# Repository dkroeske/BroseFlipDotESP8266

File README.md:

# BroseFlipDotESP8266

Few months ago I bought some very old and dirty Brose Vollmatrix displays also known as flip dot of disk displays. With the use of the internet I reverse engineered the internals and hooked up an ESP8266 board. Using an MQTT broker I'm able to display text and bitmaps (black and white e.g. 112x16 pixels). After some time the display will enter idle mode where is makes a nice clock. The display also contains a backlight that can be controlled using MQTT.

MQTT enabled Brose FlipDot

{
	"message": {
		"content": "DIEDERICH",
		"x": 0,
		"y": 0,
		"font": 2,
		"display_time": 20
	},
	"backlight": {
		"on": true
	}
}

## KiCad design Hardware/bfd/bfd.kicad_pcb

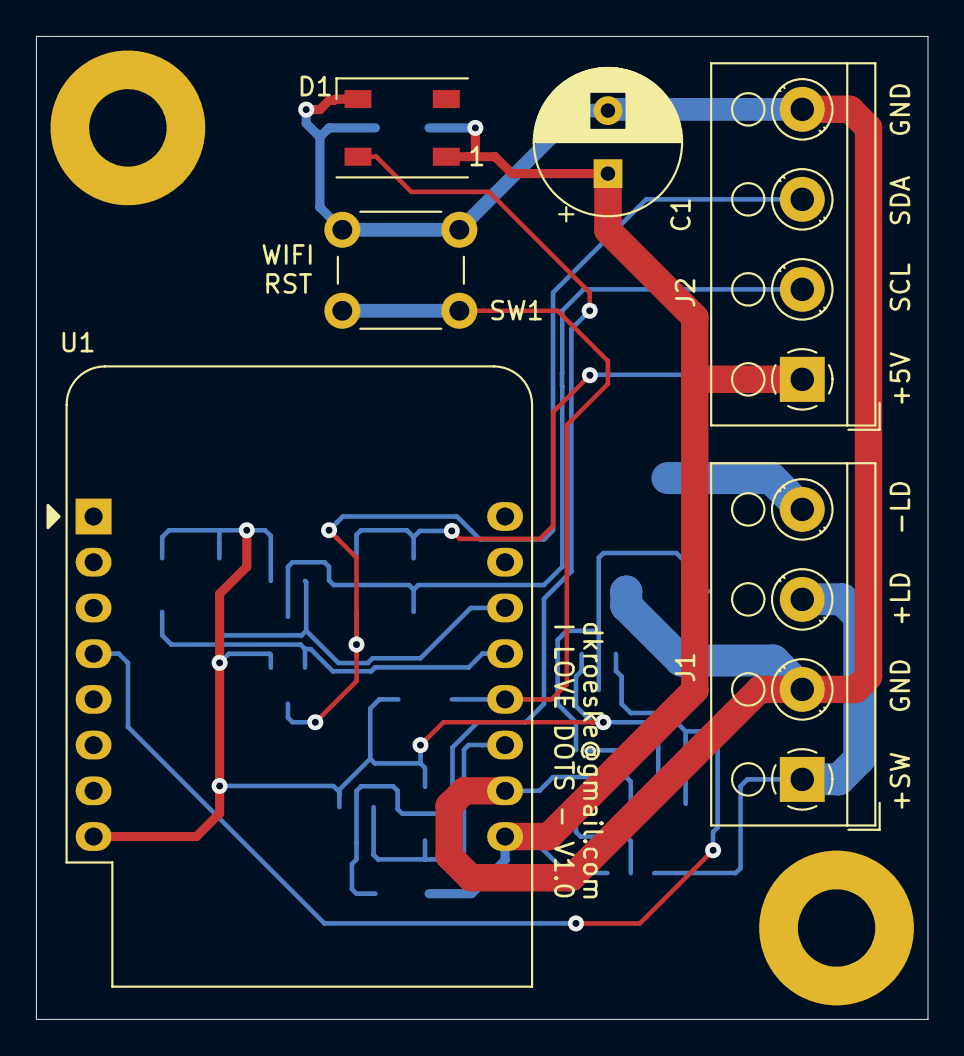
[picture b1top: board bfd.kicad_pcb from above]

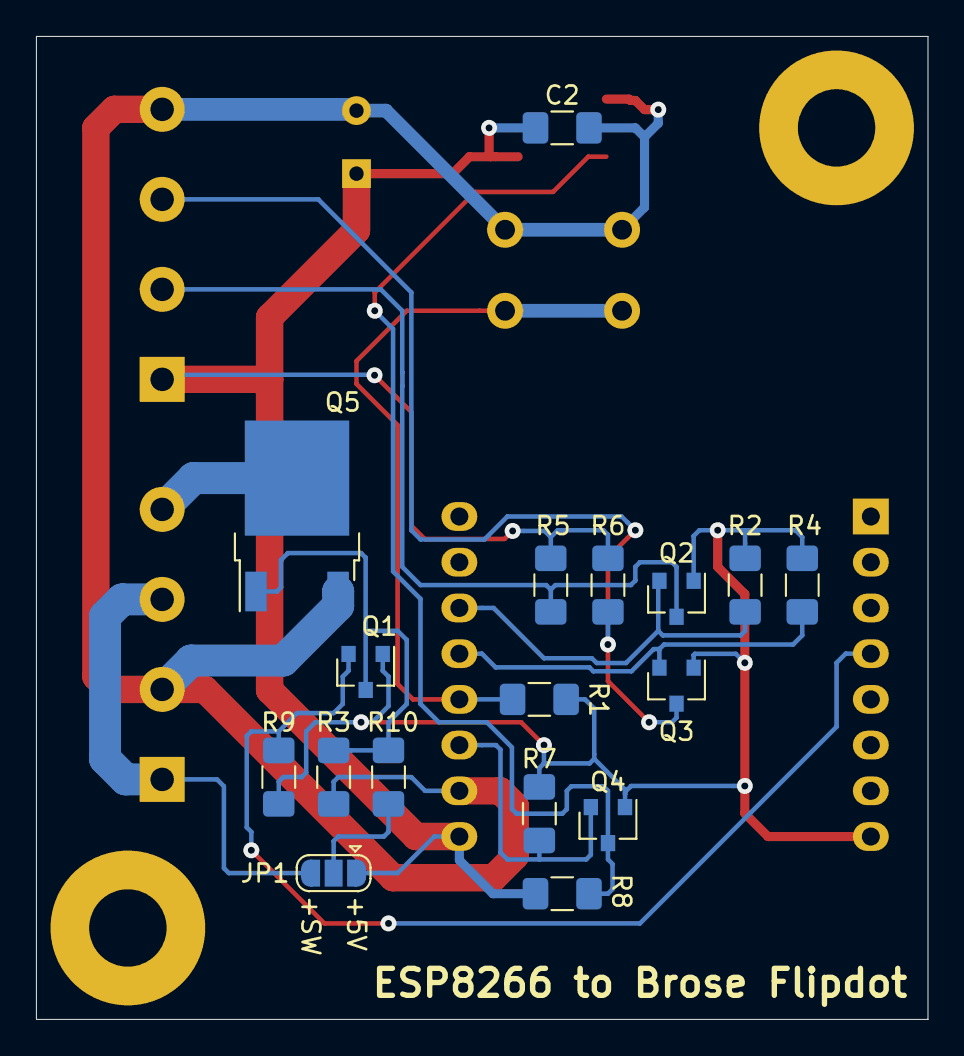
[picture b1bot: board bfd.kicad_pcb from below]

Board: 2 copper layers, 49.5 x 54.6 mm, 25 parts (17 on the bottom side), 15 nets.

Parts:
C1: 10uF/16V; CP_Radial_D8.0mm_P3.50mm
C2: 100nF; C_1206_3216Metric_Pad1.42x1.75mm_HandSolder
D1: WS2812B; LED_WS2812B_PLCC4_5.0x5.0mm_P3.2mm
H1, H2: MountingHole; MountingHole_4.3mm_M4_Pad
J1, J2: Screw_Terminal_01x04; TerminalBlock_RND_205-00003_1x04_P5.00mm_Horizontal
JP1: SolderJumper_3_Open; SolderJumper-3_P1.3mm_Open_RoundedPad1.0x1.5mm
Q1, Q2, Q3, Q4: BSS138; SOT-23
Q5: IRLR024N; TO-252-2
R1, R2, R3, R4, R5, R6, R7, R8, R9, R10: 10k; R_1206_3216Metric_Pad1.42x1.75mm_HandSolder
SW1: SW_DPST_x2; SW_PUSH_6mm
U1: WeMos_D1_mini; WEMOS_D1_mini_light

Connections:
+3V3: Q1.1, Q2.1, Q3.1, Q4.1, R1.1, R2.1, R4.1, R7.1, R9.1, U1.8
+5V: C1.1, C2.1, D1.1, J2.1, JP1.1, R5.1, R6.1, R8.1, U1.9
/BL: Q1.2, R9.2, U1.4
/LED: Q4.2, R7.2, U1.11
/RST: R1.2, SW1.2, U1.12
/SCL: Q2.2, R2.2, U1.14
/SCL_5V: J2.2, Q2.3, R5.2
/SDA: Q3.2, R4.2, U1.13
/SDA_5V: J2.3, Q3.3, R6.2
GND: C1.2, C2.2, D1.3, J1.2, J2.4, Q5.3, R3.2, SW1.1, U1.10
unnamed: D1.4, Q4.3, R8.2
unnamed: J1.1, J1.3, JP1.3
unnamed: J1.4, Q5.2
unnamed: JP1.2, R10.1
unnamed: Q1.3, Q5.1, R3.1, R10.2

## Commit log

2019-09-01 Initial commit - Code is working. Hardware is working
2019-09-01 Added README.md
